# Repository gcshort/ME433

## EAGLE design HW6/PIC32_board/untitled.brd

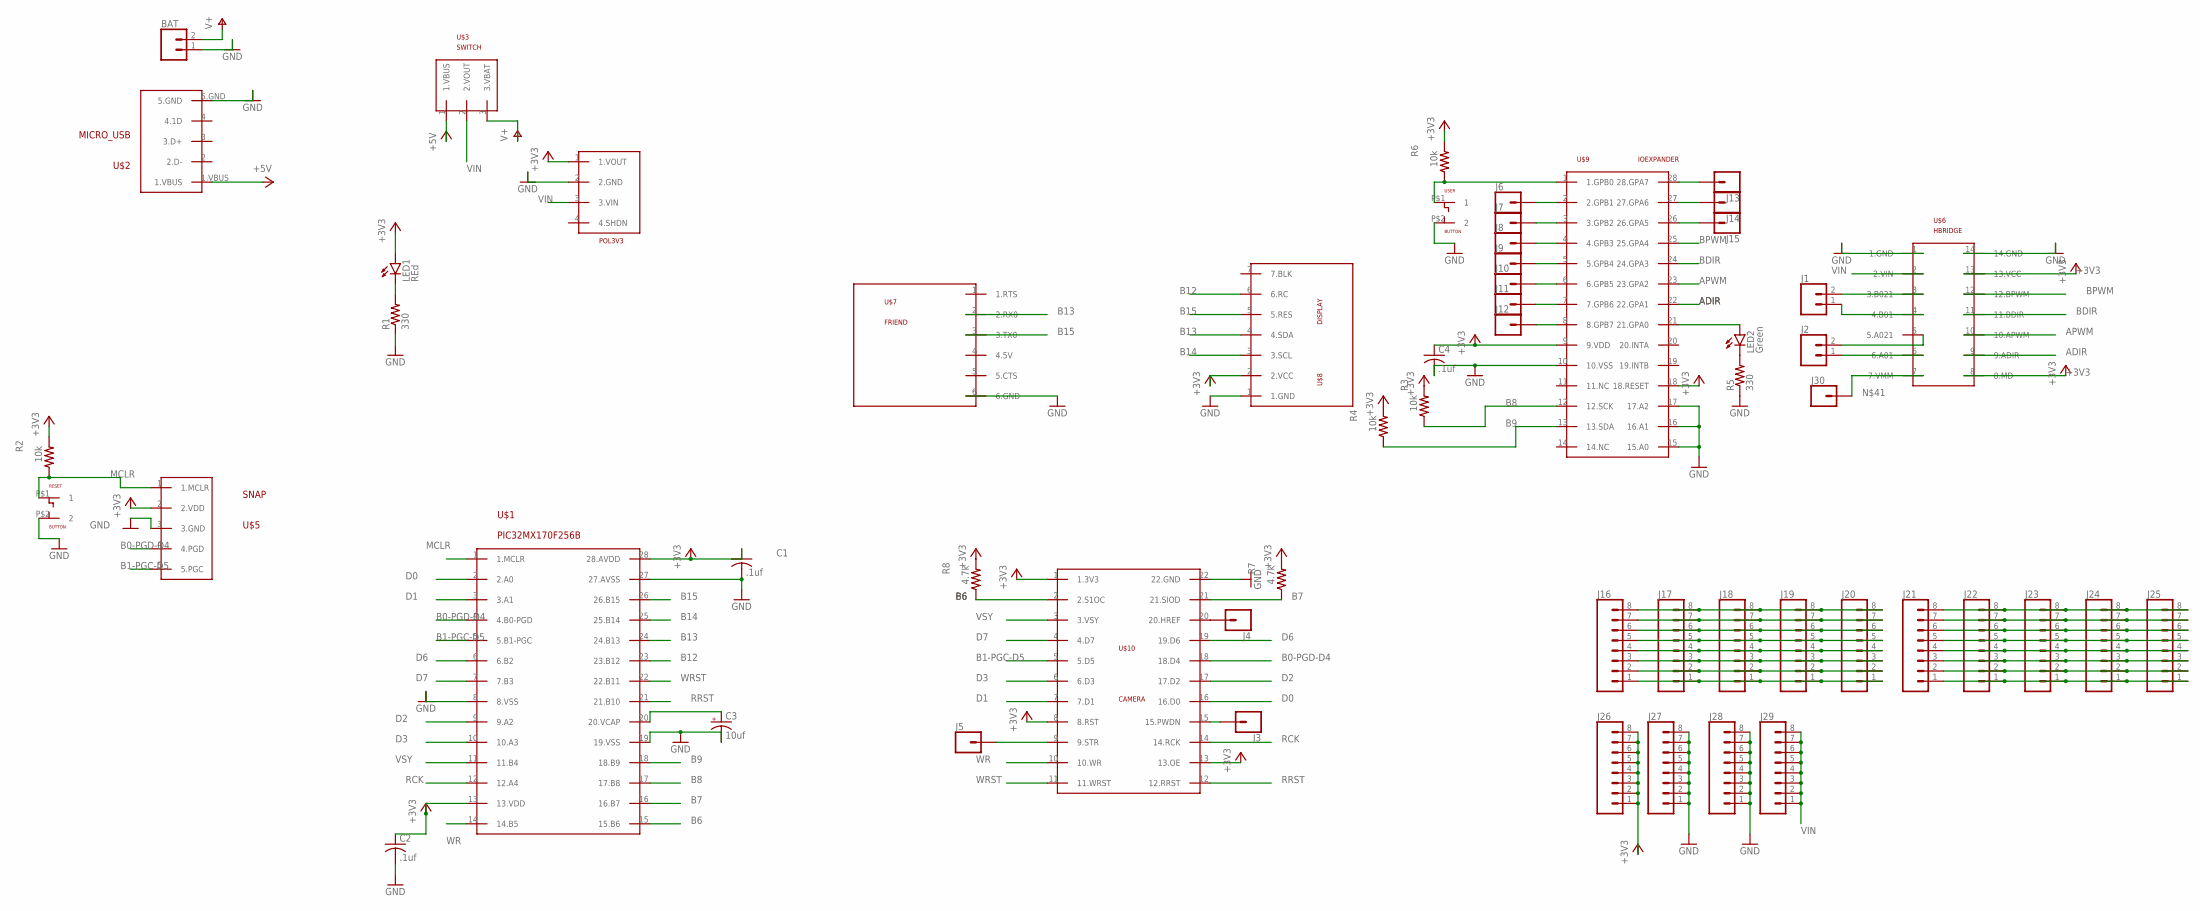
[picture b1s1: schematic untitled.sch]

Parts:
BAT: CONN_02; 1X02
C1, C2, C4: .1uf; C025-030X050
C3: 10uf; B45181B
J1, J2: CONN_02; 1X02
J3, J4, J5, J6, J7, J8, J9, J10, J11, J12, J13, J14, J15, J30: CONN_01; 1X01
J16, J17, J18, J19, J20, J21, J22, J23, J24, J25, J26, J27, J28, J29: CONN_08"; 1X08
LED1: REd; LED3MM
LED2: Green; LED3MM
R1, R5: 330; 0207/10
R2, R3, R4, R6: 10k; 0207/10
R7, R8: 4.7k; 0207/10
RESET: BUTTON
U$1: PIC32MX170F256B; DIL28-3
U$2: MICRO_USB
U$3: SWITCH; SLIDE
U$4: POL3V3
U$5: SNAP
U$6: HBRIDGE
U$7: FRIEND
U$8: DISPLAY
U$9: IOEXPANDER; DIL28-3
U$10: CAMERA
USER: BUTTON

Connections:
+3V3: C1.1, C2.1, C4.1, J26.1, J26.2, J26.3, J26.4, J26.5, J26.6, J26.7, J26.8, LED1.A, R2.2, R3.2, R4.2, R6.2, R7.2, R8.2, U$1.13 (13.VDD), U$1.28 (28.AVDD), U$4.1 (1.VOUT), U$5.2 (2.VDD), U$6.8 (8.MD), U$6.13 (13.VCC), U$8.2 (2.VCC), U$9.9 (9.VDD), U$9.18 (18.RESET), U$10.1 (1.3V3), U$10.8 (8.RST), U$10.13 (13.OE)
+5V: U$2.1.VBUS, U$3.1 (1.VBUS)
ADIR: U$6.9 (9.ADIR), U$9.22 (22.GPA1)
APWM: U$6.10 (10.APWM), U$9.23 (23.GPA2)
B0-PGD-D4: U$1.4 (4.B0-PGD), U$5.4 (4.PGD), U$10.18 (18.D4)
B1-PGC-D5: U$1.5 (5.B1-PGC), U$5.5 (5.PGC), U$10.5 (5.D5)
B6: R8.1, U$1.15 (15.B6), U$10.2 (2.S1OC)
B7: R7.1, U$1.16 (16.B7), U$10.21 (21.SIOD)
B8: R3.1, U$1.17 (17.B8), U$9.12 (12.SCK)
B9: R4.1, U$1.18 (18.B9), U$9.13 (13.SDA)
B12: U$1.23 (23.B12), U$8.6 (6.RC)
B13: U$1.24 (24.B13), U$7.2 (2.RX0), U$8.4 (4.SDA)
B14: U$1.25 (25.B14), U$8.3 (3.SCL)
B15: U$1.26 (26.B15), U$7.3 (3.TX0), U$8.5 (5.RES)
BDIR: U$6.11 (11.BDIR), U$9.24 (24.GPA3)
BPWM: U$6.12 (12.BPWM), U$9.25 (25.GPA4)
D0: U$1.2 (2.A0), U$10.16 (16.D0)
D1: U$1.3 (3.A1), U$10.7 (7.D1)
D2: U$1.9 (9.A2), U$10.17 (17.D2)
D3: U$1.10 (10.A3), U$10.6 (6.D3)
D6: U$1.6 (6.B2), U$10.19 (19.D6)
D7: U$1.7 (7.B3), U$10.4 (4.D7)
GND: BAT.1, C1.2, C2.2, C3.-, C4.2, J27.1, J27.2, J27.3, J27.4, J27.5, J27.6, J27.7, J27.8, J28.1, J28.2, J28.3, J28.4, J28.5, J28.6, J28.7, J28.8, R1.1, R5.1, RESET.P$2 (2), U$1.8 (8.VSS), U$1.19 (19.VSS), U$1.27 (27.AVSS), U$2.5.GND, U$4.2 (2.GND), U$5.3 (3.GND), U$6.1 (1.GND), U$6.14 (14.GND), U$7.6 (6.GND), U$8.1 (1.GND), U$9.10 (10.VSS), U$9.15 (15.A0), U$9.16 (16.A1), U$9.17 (17.A2), U$10.22 (22.GND), USER.P$2 (2)
MCLR: R2.1, RESET.P$1 (1), U$1.1 (1.MCLR), U$5.1 (1.MCLR)
MCLR1: R6.1, U$9.1 (1.GPB0), USER.P$1 (1)
unnamed: LED1.K (C), R1.2
unnamed: C3.+, U$1.20 (20.VCAP)
unnamed: LED2.A, U$9.21 (21.GPA0)
unnamed: J16.8, J17.8, J18.8, J19.8, J20.8
unnamed: LED2.K (C), R5.2
unnamed: J13.1, U$9.28 (28.GPA7)
unnamed: J4.1, U$10.20 (20.HREF)
unnamed: J5.1, U$10.9 (9.STR)
unnamed: J3.1, U$10.15 (15.PWDN)
unnamed: J6.1, U$9.2 (2.GPB1)
unnamed: J7.1, U$9.3 (3.GPB2)
unnamed: J8.1, U$9.4 (4.GPB3)
unnamed: J9.1, U$9.5 (5.GPB4)
unnamed: J10.1, U$9.6 (6.GPB5)
unnamed: J11.1, U$9.7 (7.GPB6)
unnamed: J12.1, U$9.8 (8.GPB7)
unnamed: J14.1, U$9.27 (27.GPA6)
unnamed: J15.1, U$9.26 (26.GPA5)
unnamed: J16.7, J17.7, J18.7, J19.7, J20.7
unnamed: J16.6, J17.6, J18.6, J19.6, J20.6
unnamed: J16.5, J17.5, J18.5, J19.5, J20.5
unnamed: J16.4, J17.4, J18.4, J19.4, J20.4
unnamed: J16.3, J17.3, J18.3, J19.3, J20.3
unnamed: J16.2, J17.2, J18.2, J19.2, J20.2
unnamed: J16.1, J17.1, J18.1, J19.1, J20.1
unnamed: J21.8, J22.8, J23.8, J24.8, J25.8
unnamed: J21.7, J22.7, J23.7, J24.7, J25.7
unnamed: J21.6, J22.6, J23.6, J24.6, J25.6
unnamed: J21.5, J22.5, J23.5, J24.5, J25.5
unnamed: J21.4, J22.4, J23.4, J24.4, J25.4
unnamed: J21.3, J22.3, J23.3, J24.3, J25.3
unnamed: J21.2, J22.2, J23.2, J24.2, J25.2
unnamed: J21.1, J22.1, J23.1, J24.1, J25.1
unnamed: J30.1, U$6.7 (7.VMM)
unnamed: J2.2, U$6.5 (5.A021)
unnamed: J2.1, U$6.6 (6.A01)
unnamed: J1.1, U$6.4 (4.B01)
unnamed: J1.2, U$6.3 (3.B021)
RCK: U$1.12 (12.A4), U$10.14 (14.RCK)
RRST: U$1.21 (21.B10), U$10.12 (12.RRST)
V+: BAT.2, U$3.3 (3.VBAT)
VIN: J29.1, J29.2, J29.3, J29.4, J29.5, J29.6, J29.7, J29.8, U$3.2 (2.VOUT), U$4.3 (3.VIN), U$6.2 (2.VIN)
VSY: U$1.11 (11.B4), U$10.3 (3.VSY)
WR: U$1.14 (14.B5), U$10.10 (10.WR)
WRST: U$1.22 (22.B11), U$10.11 (11.WRST)

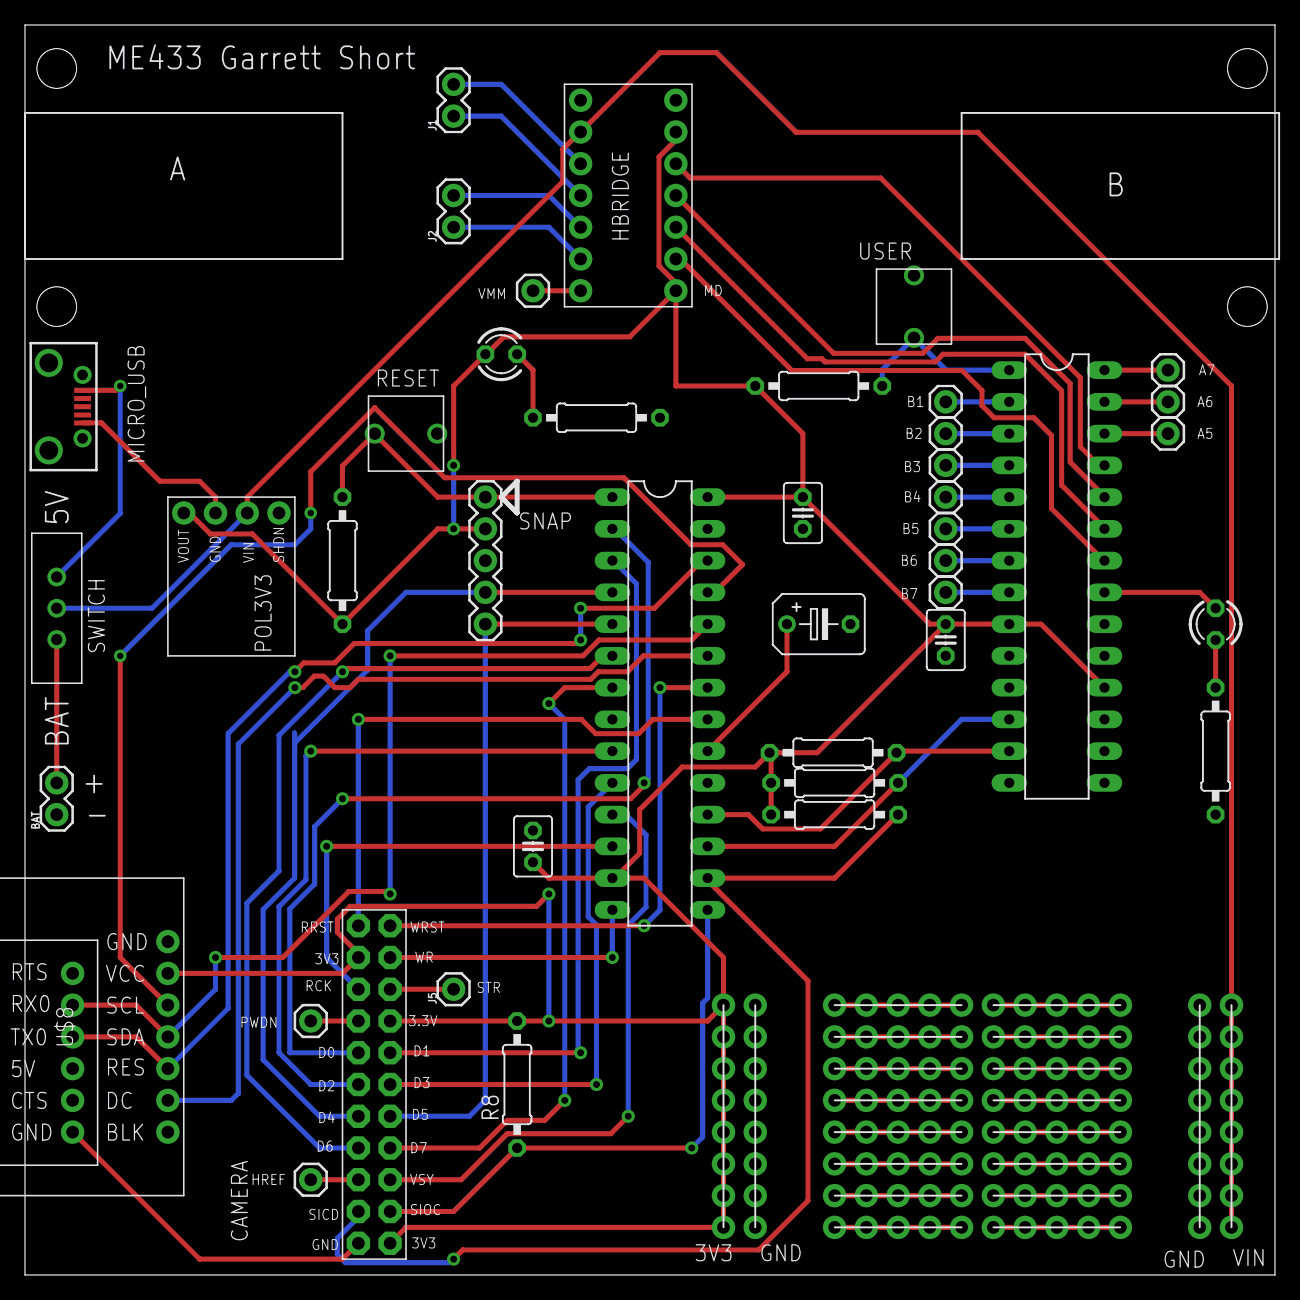
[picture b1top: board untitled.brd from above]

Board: 2 copper layers, 100.0 x 100.0 mm, 57 parts (0 on the bottom side), 70 nets.

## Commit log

2021-04-03 added starting files
2021-04-03 addede MAF and IIR code
2021-04-06 updated code and created figures
2021-04-07 added FIR
2021-04-07 added D
2021-04-09 completed hw
2021-04-30 hw10
2021-05-07 demo video
2021-05-09 hw11
2021-06-10 hw16
